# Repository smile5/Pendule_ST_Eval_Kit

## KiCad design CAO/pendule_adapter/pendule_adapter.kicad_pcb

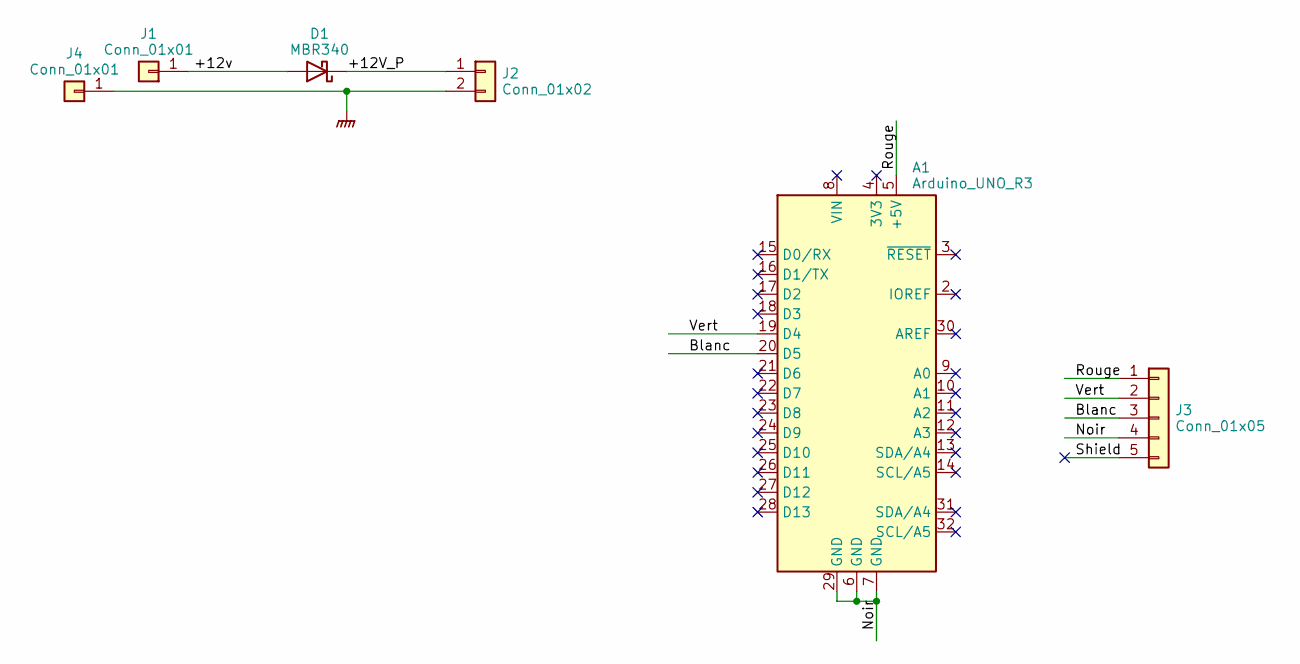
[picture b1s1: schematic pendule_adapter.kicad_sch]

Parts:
A1: Arduino_UNO_R3
D1: MBR340; D_DO-201AD_P15.24mm_Horizontal
J1, J4: Conn_01x01; Banana_Jack_1Pin
J2: Conn_01x02; TerminalBlock_bornier-2_P5.08mm
J3: Conn_01x05; TerminalBlock_bornier-5_P5.08mm

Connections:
/+12V_P: D1.1 (K), J2.1
/+12v: D1.2 (A), J1.1
/Blanc: A1.20 (D5), J3.3
/Noir: A1.6 (GND), A1.7 (GND), A1.29 (GND), J3.4
/Rouge: A1.5 (+5V), J3.1
/Shield: J3.5
/Vert: A1.19 (D4), J3.2
GNDPWR: J2.2, J4.1

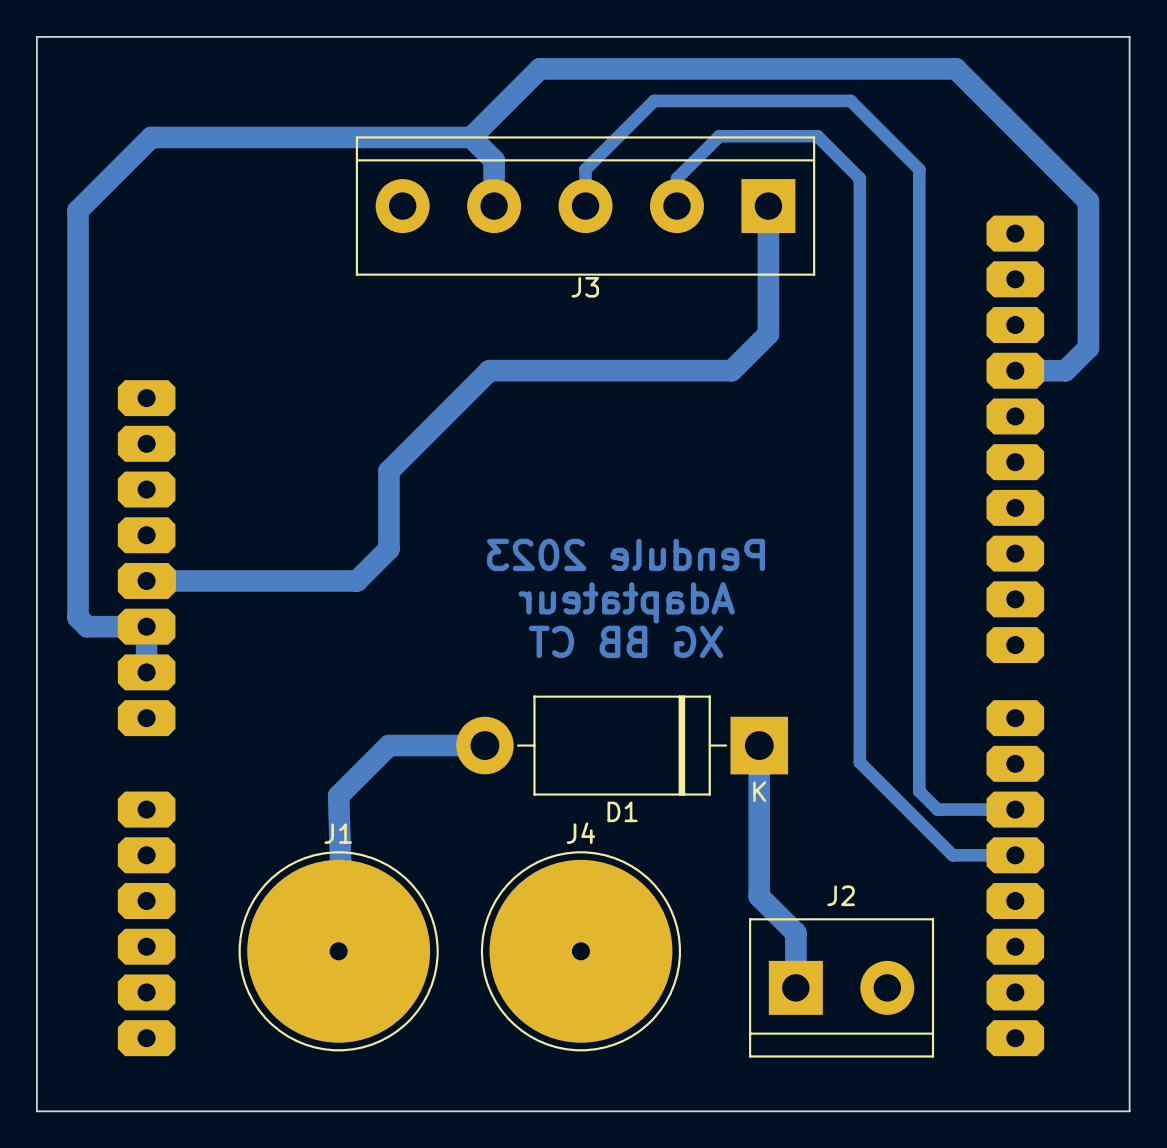
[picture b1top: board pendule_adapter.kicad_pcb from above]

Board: 2 copper layers, 60.7 x 59.7 mm, 6 parts (1 on the bottom side), 7 nets.
